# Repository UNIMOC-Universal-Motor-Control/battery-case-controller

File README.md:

# battery-case-controller
 unimoc compatible controller for Hailong battery case

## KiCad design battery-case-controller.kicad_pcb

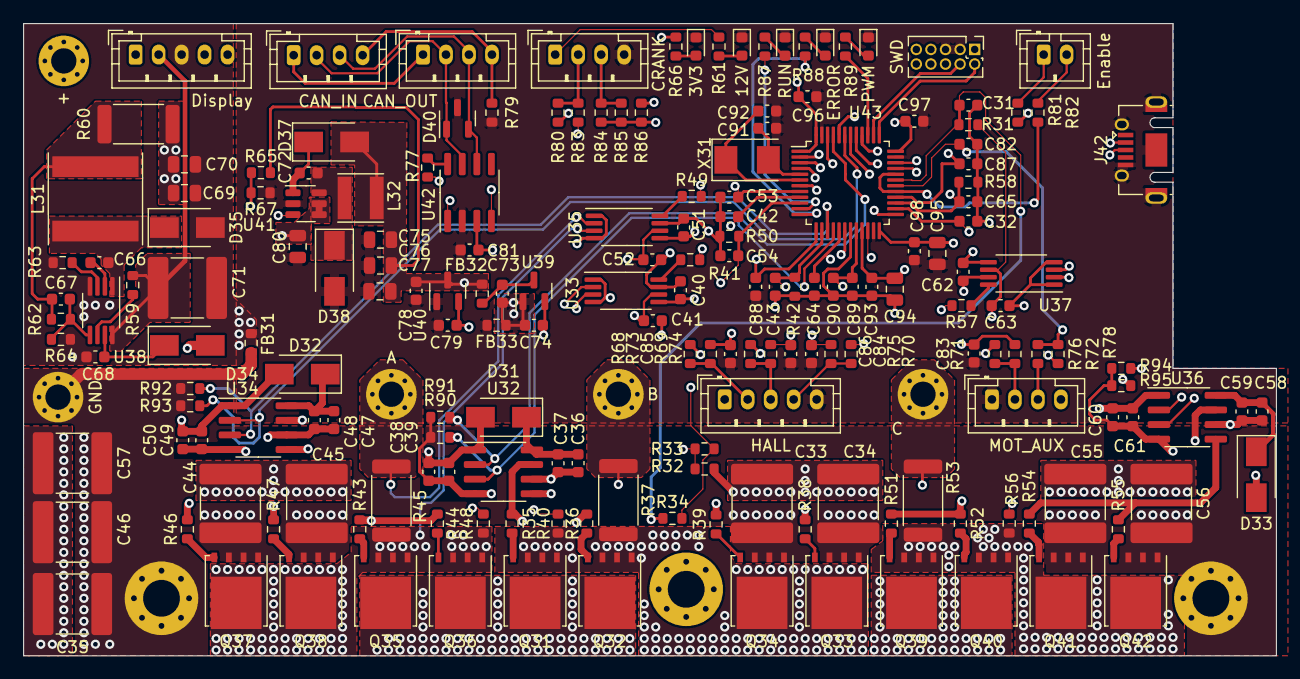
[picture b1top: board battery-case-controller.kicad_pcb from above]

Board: 6 copper layers, 109.0 x 55.0 mm, 193 parts (0 on the bottom side), 107 nets.

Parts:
C31, C32, C37, C39, C40, C41, C43, C48, C50, C51, C52, C54, C59, C61, C62, C63, C65, C66, C72, C81, C82, C90, C93, C96, C97, C98: 100n; C_0603_1608Metric
C33, C34, C35, C44, C45, C46, C55, C56, C57, C71: 10u; C_2220_5650Metric
C36, C38, C47, C49, C58, C60: 10u; C_0603_1608Metric
C42, C53, C64, C67, C83, C84, C85, C86, C87, C88: 2n2; C_0603_1608Metric
C68, C73, C74, C78, C79, C89: 1u; C_0603_1608Metric
C69, C70, C75, C76, C77, C80, C94, C95: 10u; C_0805_2012Metric
C91, C92: 15p; C_0603_1608Metric
D31, D32, D33, D34, D35, D37, D38: SS3200; D_SMA
D36: 12V; LED_0603_1608Metric
D39: 3V3; LED_0603_1608Metric
D40: ESDCAN24-2BLY; SOT-23
D41: RUN; LED_0603_1608Metric
D42: ERROR; LED_0603_1608Metric
D43: PWM; LED_0603_1608Metric
FB31, FB32, FB33: BLM18PG221SN1D; R_0603_1608Metric
J31: +; MountingHole_2.2mm_M2_Pad_Via
J32: Display; JST_PH_B5B-PH-K_1x05_P2.00mm_Vertical
J33: A; MountingHole_2.2mm_M2_Pad_Via
J34: HALL; JST_PH_B5B-PH-K_1x05_P2.00mm_Vertical
J35: B; MountingHole_2.2mm_M2_Pad_Via
J36: MOT_AUX; JST_PH_B4B-PH-K_1x04_P2.00mm_Vertical
J37: C; MountingHole_2.2mm_M2_Pad_Via
J38: CRANK; JST_PH_B4B-PH-K_1x04_P2.00mm_Vertical
J39: GND; MountingHole_2.2mm_M2_Pad_Via
J40: CAN_IN; JST_PH_B4B-PH-K_1x04_P2.00mm_Vertical
J41: CAN_OUT; JST_PH_B4B-PH-K_1x04_P2.00mm_Vertical
J42: Debug; USB_Micro-AB_Molex_47590-0001
J43: SWD; PinHeader_2x05_P1.27mm_Vertical
L31: 330u; L_Taiyo-Yuden_NR-80xx
L32: 10u; L_Taiyo-Yuden_NR-40xx
M31, M32, M33: MountingHole_Pad; MountingHole_3.2mm_M3_Pad_Via
Q31, Q32, Q33, Q34, Q35, Q36, Q37, Q38, Q39, Q40, Q41, Q42: BSC040N08; TDSON-8-1
R31, R62, R67, R72, R77, R90, R91, R92, R93, R94, R95: 10k; R_0603_1608Metric
R32, R40, R48, R56: 33k; R_0603_1608Metric
R33, R41, R42, R49, R50, R57, R58, R68, R69, R70, R71, R80, R81, R82: 1k; R_0603_1608Metric
R34: NTC 10k; R_0603_1608Metric
R35, R36, R38, R39, R43, R44, R46, R47, R51, R52, R54, R55: 22R; R_0603_1608Metric
R37, R45, R53: 0mr5; R_2512_6332Metric
R59: 220k; R_0603_1608Metric
R60: 2R2; R_2512_6332Metric
R61, R64, R73, R74, R75, R76, R78, R83, R84, R85, R86: 3k3; R_0603_1608Metric
R63: 100k; R_0603_1608Metric
R65: 56k; R_0603_1608Metric
R66, R87, R88, R89: 470R; R_0603_1608Metric
R79: 1R; R_0603_1608Metric
U31: Enable; JST_PH_B2B-PH-K_1x02_P2.00mm_Vertical
U32, U34, U36: LM5109B; SOIC-8_3.9x4.9mm_P1.27mm
U33, U35, U37: INA240A2PWR; TSSOP-8_4.4x3mm_P0.65mm
U38: LM5008; MSOP-8_3x3mm_P0.65mm
U39, U40: XC6206P332MR; SOT-23
U41: LMR12010X; SOT-23-6
U42: SN65HVD230; SOIC-8_3.9x4.9mm_P1.27mm
U43: STM32G491CxT; TQFP-48_7x7mm_P0.5mm
X31: 8MHz; Crystal_SMD_5032-2Pin_5.0x3.2mm

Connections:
+3.3VADC: C40.1, C51.1, C62.1, C74.2, C93.1, C94.1, U33.5 (V+), U35.5 (V+), U37.5 (V+), U39.2 (VO), U43.21 (VDDA)
+3V3: C79.2, C81.1, C95.1, C96.1, C97.1, C98.1, J43.1, R66.2, R68.1, R69.1, R70.1, R71.1, R80.1, R81.2, U40.2 (VO), U42.3 (VCC), U43.1 (VBAT), U43.24 (VDD), U43.36 (VDD), U43.48 (VDD)
+5V: C75.1, C76.1, C77.1, C78.2, D37.2 (A), FB32.2, J34.1, L32.2, R65.2, U40.3 (VI)
+12V: C38.1, C39.1, C49.1, C50.1, C60.1, C61.1, C69.1, C70.1, C80.1, D31.2 (A), D32.2 (A), D33.2 (A), D34.2 (A), J38.1, R60.1, R61.1, U32.1 (VDD), U34.1 (VDD), U36.1 (VDD), U41.4 (~SHDN), U41.5 (VIN)
+BATT: C33.1, C34.1, C35.1, C44.1, C45.1, C46.1, C55.1, C56.1, C57.1, J31.1, J32.1, Q31.5 (D), Q32.5 (D), Q35.5 (D), Q36.5 (D), Q39.5 (D), Q40.5 (D), R32.1
/Interface/CAN+: D40.1 (A1), J40.2, J41.2, U42.7 (CANH)
/Interface/CAN-: D40.2 (A2), J40.3, J41.3, U42.6 (CANL)
/Interface/CAN_GND: J40.4, J41.4, R79.2
/Interface/CAN_RX: U42.4 (R), U43.40 (PB3)
/Interface/CAN_SLP: R77.1, U43.44 (PB7)
/Interface/CAN_TX: U42.1 (D), U43.41 (PB4)
/Interface/ENABLE+: R81.1, U31.1
/Interface/ENABLE-: R82.1, U31.2
/Interface/HALL_A: C85.1, R73.1, U43.2 (PC13)
/Interface/HALL_A_IN: J34.2, R68.2, R73.2
/Interface/HALL_B: C86.1, R74.1, U43.3 (OSC32_IN/PC14)
/Interface/HALL_B_IN: J34.3, R69.2, R74.2
/Interface/HALL_C: C84.1, R75.1, U43.4 (OSC32_OUT/PC15)
/Interface/HALL_C_IN: J34.4, R70.2, R75.2
/Interface/PULSE_CRK: C88.1, R83.1, U43.13 (PA5)
/Interface/PULSE_CRK_IN: J38.2, R80.2, R83.2
/Interface/PULSE_MOT: C83.1, R76.1, U43.18 (PB2)
/Interface/PULSE_MOT_IN: J36.2, R71.2, R76.2
/Interface/PWM_BREAK: R82.2, U43.29 (PB15), U43.32 (PA10)
/Interface/TEMP_MOT: C82.1, R72.2, R78.1, U43.30 (PA8)
/Interface/TEMP_MOT_IN: J36.3, R78.2
/Interface/TORQ_CRK: C87.1, R84.1, R85.1, R86.2, U43.28 (PB14)
/Interface/TORQ_CRK_IN: J38.3, R84.2, R85.2
/Interface/VREF: C41.1, C52.1, C63.1, C89.1, C90.1, R31.1, R72.1, U33.6 (REF2), U35.6 (REF2), U37.6 (REF2), U43.20 (VREF+)
/mcu/AIN_IA: C53.1, R49.2, U43.8 (PA0)
/mcu/AIN_IB: C42.1, R41.2, U43.9 (PA1)
/mcu/AIN_IC: C64.1, R57.2, U43.17 (PB1)
/mcu/AIN_TEMP: C31.1, R31.2, R34.1, U43.31 (PA9)
/mcu/AIN_VA: C54.1, R48.2, R50.1, U43.10 (PA2)
/mcu/AIN_VB: C43.1, R40.2, R42.1, U43.14 (PA6)
/mcu/AIN_VC: C65.1, R56.2, R58.1, U43.27 (PB13)
/mcu/AIN_VDC: C32.1, R32.2, R33.1, U43.26 (PB12)
/mcu/DISP_RX: J32.5, U43.25 (PB11)
/mcu/DISP_TX: J32.4, U43.22 (PB10)
/mcu/NRST: J43.10, U43.7 (~NRST/PG10)
/mcu/PWM_A: R93.1, U34.2 (HI), U43.43 (PB6)
/mcu/PWM_AN: R92.1, U34.3 (LI), U43.15 (PA7)
/mcu/PWM_B: R91.1, U32.2 (HI), U43.45 (PB8/BOOT0)
/mcu/PWM_BN: R90.1, U32.3 (LI), U43.16 (PB0)
/mcu/PWM_C: R95.1, U36.2 (HI), U43.46 (PB9)
/mcu/PWM_CN: R94.1, U36.3 (LI), U43.42 (PB5)
/mcu/SWD_CLK: J43.4, U43.38 (PA14)
/mcu/SWD_IO: J43.2, U43.37 (PA13)
/mcu/USB_D+: J42.3 (D+), U43.34 (PA12/USB_DP)
/mcu/USB_D-: J42.2 (D-), U43.33 (PA11/USB_DM)
/phase_a/Phase: J33.1, R45.1, U35.2 (+)
/phase_b/Phase: J35.1, R37.1, U33.2 (+)
/phase_c/Phase: J37.1, R53.1, U37.2 (+)
/power_supply/DCDC_VIN: C71.1, J32.2, R59.2, U38.8 (VIN)
GNDA: C31.2, C32.2, C40.2, C41.2, C42.2, C43.2, C51.2, C52.2, C53.2, C54.2, C62.2, C63.2, C64.2, C65.2, C73.1, C74.1, C82.2, C87.2, C89.2, C90.2, C93.2, C94.2, FB33.1, J36.4, R33.2, R34.2, R42.2, R50.2, R58.2, R86.1, U33.1 (GND), U33.4 (GND), U33.7 (REF1), U35.1 (GND), U35.4 (GND), U35.7 (REF1), U37.1 (GND), U37.4 (GND), U37.7 (REF1), U39.1 (GND), U43.19 (VSSA)
GNDD: C68.1, C69.2, C70.2, C71.2, C75.2, C76.2, C77.2, C78.1, C79.1, C80.2, C81.2, C83.2, C84.2, C85.2, C86.2, C88.2, C91.2, C92.2, C95.2, C96.2, C97.2, C98.2, D35.2 (A), D36.1 (K), D38.2 (A), D39.1 (K), D40.3 (common), D41.1 (K), D42.1 (K), D43.1 (K), FB31.1, FB33.2, J32.3, J34.5, J36.1, J38.4, J42.5 (GND), J42.6 (Shield), J43.3, J43.5, R63.1, R64.1, R67.1, R79.1, U38.4 (RTN), U40.1 (GND), U41.2 (GND), U42.2 (GND), U43.23 (VSS), U43.35 (VSS), U43.47 (VSS)
GNDPWR: C33.2, C34.2, C35.2, C38.2, C39.2, C44.2, C45.2, C46.2, C49.2, C50.2, C55.2, C56.2, C57.2, C60.2, C61.2, FB31.2, J39.1, M31.1, M32.1, M33.1, Q33.1 (S), Q33.2 (S), Q33.3 (S), Q34.1 (S), Q34.2 (S), Q34.3 (S), Q37.1 (S), Q37.2 (S), Q37.3 (S), Q38.1 (S), Q38.2 (S), Q38.3 (S), Q41.1 (S), Q41.2 (S), Q41.3 (S), Q42.1 (S), Q42.2 (S), Q42.3 (S), R90.2, R91.2, R92.2, R93.2, R94.2, R95.2, U32.4 (VSS), U34.4 (VSS), U36.4 (VSS)
unnamed: C36.1, C37.1, D31.1 (K), U32.8 (HB)
unnamed: C36.2, C37.2, Q31.1 (S), Q31.2 (S), Q31.3 (S), Q32.1 (S), Q32.2 (S), Q32.3 (S), Q33.5 (D), Q34.5 (D), R37.2, R40.1, U32.6 (HS), U33.3 (-)
unnamed: C47.1, C48.1, D32.1 (K), U34.8 (HB)
unnamed: C47.2, C48.2, Q35.1 (S), Q35.2 (S), Q35.3 (S), Q36.1 (S), Q36.2 (S), Q36.3 (S), Q37.5 (D), Q38.5 (D), R45.2, R48.1, U34.6 (HS), U35.3 (-)
unnamed: C58.1, C59.1, D33.1 (K), U36.8 (HB)
unnamed: C58.2, C59.2, Q39.1 (S), Q39.2 (S), Q39.3 (S), Q40.1 (S), Q40.2 (S), Q40.3 (S), Q41.5 (D), Q42.5 (D), R53.2, R56.1, U36.6 (HS), U37.3 (-)
unnamed: C66.1, D35.1 (K), L31.1, U38.1 (SW)
unnamed: C66.2, U38.2 (BST)
unnamed: C67.1, L31.2, R60.2, R62.2
unnamed: C67.2, R62.1, R64.2, U38.5 (FB)
unnamed: C68.2, D34.1 (K), U38.7 (VCC)
unnamed: C72.1, D38.1 (K), L32.1, U41.6 (SW)
unnamed: C72.2, D37.1 (K), U41.1 (CB)
unnamed: C73.2, FB32.1, U39.3 (VI)
unnamed: C91.1, U43.5 (OSC_IN/PF0), X31.2
unnamed: C92.1, U43.6 (OSC_OUT/PF1), X31.1
unnamed: D36.2 (A), R61.2
unnamed: D39.2 (A), R66.1
unnamed: D41.2 (A), R87.1
unnamed: D42.2 (A), R88.1
unnamed: D43.2 (A), R89.1
unnamed: J40.1, J41.1
unnamed: Q31.4 (G), R35.1
unnamed: Q32.4 (G), R36.1
unnamed: Q33.4 (G), R38.1
unnamed: Q34.4 (G), R39.1
unnamed: Q35.4 (G), R43.1
unnamed: Q36.4 (G), R44.1
unnamed: Q37.4 (G), R46.1
unnamed: Q38.4 (G), R47.1
unnamed: Q39.4 (G), R51.1
unnamed: Q40.4 (G), R52.1
unnamed: Q41.4 (G), R54.1
unnamed: Q42.4 (G), R55.1
unnamed: R35.2, R36.2, U32.7 (HO)
unnamed: R38.2, R39.2, U32.5 (LO)
unnamed: R41.1, U33.8
unnamed: R43.2, R44.2, U34.7 (HO)
unnamed: R46.2, R47.2, U34.5 (LO)
unnamed: R49.1, U35.8
unnamed: R51.2, R52.2, U36.7 (HO)
unnamed: R54.2, R55.2, U36.5 (LO)
unnamed: R57.1, U37.8
unnamed: R59.1, U38.6 (RON/SD)
unnamed: R63.2, U38.3 (RCL)
unnamed: R65.1, R67.2, U41.3 (FB)
unnamed: R77.2, U42.8 (Rs)
unnamed: R87.2, U43.11 (PA3)
unnamed: R88.2, U43.12 (PA4)
unnamed: R89.2, U43.39 (PA15)

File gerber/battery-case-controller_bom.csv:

"ID";"Bezeichner";"Gehäuse";"Stückzahl";"Bezeichnung";"Anbieter und Referenz";
1;"C65,C82,C72,C96,C54,C59,C81,C52,C97,C98,C63,C39,C62,C50,C40,C48,C32,C90,C93,C43,C51,C66,C61,C41,C31,C37";"C_0603_1608Metric";26;"100n";;;
2;"R35,R44,R39,R46,R38,R36,R55,R52,R54,R51,R47,R43";"R_0603_1608Metric";12;"22R";;;
3;"R48,R56,R40,R32";"R_0603_1608Metric";4;"33k";;;
4;"R89,R87,R88,R66";"R_0603_1608Metric";4;"470R";;;
5;"C89,C74,C79,C78,C68,C73";"C_0603_1608Metric";6;"1u";;;
6;"C94,C69,C75,C95,C80,C70,C76,C77";"C_0805_2012Metric";8;"10u";;;
7;"X31";"Crystal_SMD_5032-2Pin_5.0x3.2mm";1;"8MHz";;;
8;"R63";"R_0603_1608Metric";1;"100k";;;
9;"D40";"SOT-23";1;"ESDCAN24-2BLY";;;
10;"R84,R76,R74,R61,R86,R75,R64,R85,R83,R73,R78";"R_0603_1608Metric";11;"3k3";;;
11;"C86,C85,C67,C64,C88,C87,C83,C42,C84,C53";"C_0603_1608Metric";10;"2n2";;;
12;"J39";"MountingHole_2.2mm_M2_Pad_Via";1;"GND";;;
13;"U37,U35,U33";"TSSOP-8_4.4x3mm_P0.65mm";3;"INA240A2PWR";;;
14;"Q40,Q41,Q35,Q31,Q38,Q33,Q42,Q32,Q37,Q34,Q39,Q36";"TDSON-8-1";12;"BSC040N08";;;
15;"U40,U39";"SOT-23";2;"XC6206P332MR";;;
16;"R71,R70,R33,R49,R80,R58,R69,R50,R41,R82,R81,R68,R57,R42";"R_0603_1608Metric";14;"1k";;;
17;"C44,C35,C45,C56,C71,C34,C33,C46,C55,C57";"C_2220_5650Metric";10;"10u";;;
18;"R53,R37,R45";"R_2512_6332Metric";3;"0mr5";;;
19;"U34,U36,U32";"SOIC-8_3.9x4.9mm_P1.27mm";3;"LM5109B";;;
20;"J36";"JST_PH_B4B-PH-K_1x04_P2.00mm_Vertical";1;"MOT_AUX";;;
21;"J32";"JST_PH_B5B-PH-K_1x05_P2.00mm_Vertical";1;"DISPLAY";;;
22;"L32";"L_Taiyo-Yuden_NR-40xx";1;"10u";;;
23;"M33,M31,M32";"MountingHole_3.2mm_M3_Pad_Via";3;"MountingHole_Pad";;;
24;"C36,C47,C58,C38,C60,C49";"C_0603_1608Metric";6;"10u";;;
25;"D35,D37,D33,D31,D34,D38,D32";"D_SMA";7;"SS3200";;;
26;"D36";"LED_0603_1608Metric";1;"12V";;;
27;"R79";"R_0603_1608Metric";1;"1R";;;
28;"J41";"JST_PH_B4B-PH-K_1x04_P2.00mm_Vertical";1;"CAN_OUT";;;
29;"U31";"JST_PH_B2B-PH-K_1x02_P2.00mm_Vertical";1;"Enable";;;
30;"D39";"LED_0603_1608Metric";1;"3V3";;;
31;"R65";"R_0603_1608Metric";1;"56k";;;
32;"J34";"JST_PH_B5B-PH-K_1x05_P2.00mm_Vertical";1;"HALL";;;
33;"FB33,FB32,FB31";"R_0603_1608Metric";3;"BLM18PG221SN1D";;;
34;"D43";"LED_0603_1608Metric";1;"PWM";;;
35;"R31,R67,R62,R72,R77";"R_0603_1608Metric";5;"10k";;;
36;"L31";"L_Taiyo-Yuden_NR-80xx";1;"330u";;;
37;"C91,C92";"C_0603_1608Metric";2;"15p";;;
38;"J40";"JST_PH_B4B-PH-K_1x04_P2.00mm_Vertical";1;"CAN_IN";;;
39;"R34";"R_0603_1608Metric";1;"NTC 10k";;;
40;"J42";"USB_Micro-AB_Molex_47590-0001";1;"Debug";;;
41;"U41";"SOT-23-6";1;"LMR12010X";;;
42;"U42";"SOIC-8_3.9x4.9mm_P1.27mm";1;"SN65HVD230";;;
43;"J43";"PinHeader_2x05_P1.27mm_Vertical";1;"SWD";;;
44;"U38";"MSOP-8_3x3mm_P0.65mm";1;"LM5008";;;
45;"R60";"R_2512_6332Metric";1;"2R2";;;
46;"J37";"MountingHole_2.2mm_M2_Pad_Via";1;"C";;;
47;"U43";"TQFP-48_7x7mm_P0.5mm";1;"STM32G491CxT";;;
48;"D41";"LED_0603_1608Metric";1;"RUN";;;
49;"J35";"MountingHole_2.2mm_M2_Pad_Via";1;"B";;;
50;"J38";"JST_PH_B4B-PH-K_1x04_P2.00mm_Vertical";1;"CRANK";;;
51;"D42";"LED_0603_1608Metric";1;"ERR";;;
52;"R59";"R_0603_1608Metric";1;"220k";;;
53;"J33";"MountingHole_2.2mm_M2_Pad_Via";1;"A";;;
54;"J31";"MountingHole_2.2mm_M2_Pad_Via";1;"+";;;

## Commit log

2022-12-05 next round for schematic
2022-12-06 finished schematics
2022-12-07 Placing first round finished
2022-12-07 layout
2022-12-07 next round routing
2022-12-08 just the silk open
2022-12-08 Ordered
2023-01-17 Fixed SWD connector spacing and fit of pcb to housing
2023-01-17 Fixed pinning error for Display RX and PWM Break
2023-01-20 added Pulldowns to the PWM wires
2025-05-23 added datasheet for the controller
2025-05-23 added start of a cmake modm project to support the hardware
2025-05-23 added vscode config
2025-05-23 add google clang-format as basis
2025-05-23 vscode configuration provider and format
2025-05-23 added adc test code
